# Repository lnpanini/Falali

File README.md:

# Falali — a 30.007 project

An AMR-style **under-ride platform** that drives beneath a textile trolley, uses upward-facing
time-of-flight sensors to confirm it is under the trolley and centred, **clamps** onto the
underside, and then moves the trolley. ESP32-S3 firmware, hardware and documentation.

This is also the whole-project home for **Falali — One AMR Fits All** (SUTD 30.007 Engineering
Design Innovation, Group 10): a low-profile autonomous mobile robot that moves existing fabric
trolleys in a textile factory by driving *underneath* them, clamping on, and transporting them —
no changes to the trolleys or the factory floor.

- **Controller:** ESP32-S3-WROOM-1 **N16R8** (16 MB flash, 8 MB octal PSRAM)
- **No** LiDAR, camera, ROS 2, SLAM, or mapping.

> **Hardware documentation lives in [`docs/hardware/`](docs/hardware/)** — power-up runbook,
> component list, per-connector pinouts for all three PCBs (extracted from the KiCad netlists, not
> inferred), and a fabrication/repair guide. [`docs/hardware-architecture.md`](docs/hardware-architecture.md)
> is the older companion and is partly superseded by it. The pin table further down this README is
> the *pre-PCB design intent* and does **not** match the fabricated board.

Full design: [`docs/superpowers/specs/2026-07-06-falali-esp32-docking-design.md`](docs/superpowers/specs/2026-07-06-falali-esp32-docking-design.md).

## Results against requirements

| Requirement | Target | Result |
|---|---|---|
| Fit under trolley clearance | ≤ 200 mm | **167 mm**, validated on the physical chassis |
| Move loaded trolley | ≥ 100 kg | **Passed — load moved with two people standing on top** |
| Clamp holding force | ≥ 300 N | Weakest-link analysis: clamp capacity 403 N (SF 1.34×) |
| Clamp vertical reach | ≥ 200 mm | Met |
| Docking time | ≤ 1 min | Under 60 s in testing |
| Worst-case castor misalignment | All 4 orientations | Moves under all |

Derivations, test protocols and data: [`docs/pdr-falali-amr.pdf`](docs/pdr-falali-amr.pdf)
(Preliminary Design Review deck, 11 Aug 2026).

## Delivered system

```
ESP-BASE (Wheel Drive PCB)                  ESP-ARM (Arm Subsystem PCB)
docking state machine                       arm axes X/Y, flipper servos, clamp
mecanum mixing, 4× corner ToF centring   ⇄  limit switches, homing
clamp handoff                             ESP-NOW over Wi-Fi (channel 1)

operator: BLE gamepad ([bench_ble/](bench_ble/))
```

Commercial AMRs don't fit this job: platform AMRs are too tall to get under the trolleys, tow
tractors need turning space, side-docking systems need the trolley modified. The answer is
**under-entry capture**: fit under the ≤200 mm clearance, strafe beneath an existing trolley with
mecanum drive, confirm centring sensor-only, clamp and carry.

## Safety principle

**The clamp must not engage unless the alignment logic CONFIRMS the platform is centred.** Limit
switches only confirm clamp *travel*; they never authorise clamping. `SafetyMonitor` is the single
gate (`confirmed && no faults && !E-stop`), and the docking state machine reaches the clamp handoff
only after a sustained `CONFIRM`. The clamp/arm mechanism itself is an **external subsystem** that
plugs in at the `IClamp` port.

## Architecture — hexagonal (ports & adapters)

```
lib/ports      pure C++ interfaces + shared types (no Arduino)
lib/domain     the hand-written core:  CornerEdgeDetector · DeadReckonOdometry · SafetyMonitor · DockingStateMachine
lib/drive      MecanumDrive (mixes body-frame vx/vy/omega -> 4 wheels)
lib/fakes      desktop test doubles for every port
lib/hal_esp32  Arduino adapters over popular libraries
include/       config.h (tunables) · pins.h (GPIO map)
src/main.cpp   composition root: builds adapters, wires domain, runs the loop
test/          host unit tests (Unity)
```

Dependency rule: **domain → ports** only; **adapters → ports**; **main → everything**. The domain
never includes Arduino, so it compiles and tests on a laptop. Commodity work uses popular libraries
(`pololu/VL53L0X`, `Bounce2`, `ArduinoJson`, `SerialCommands`, ESP32 `LEDC`); only the docking
sequence, corner edge detection, odometry, and safety logic are hand-written — and that is the part
under test.

**Alignment method:** with a solid trolley board and 4 corner ToF sensors, docking is a deterministic
geometric sequence — `APPROACH → ORIENT` (rotate until both front corners see the edge) `→ CENTER_X`
(odometry-centre between near/far edges) `→ CENTER_Y` (same, strafing) `→ CONFIRM → clamp handoff`.
Centring uses dead-reckoning odometry; driving to the midpoint between two edge events makes it robust
to calibration error.

**ToF wiring, both ESPs:** all four corner sensors keep their factory address `0x29` and are brought
up one at a time via **XSHUT re-addressing** — `Vl53l0xArray` on the base, `TofSensorArray` in
`arm/`. An earlier design multiplexed them through the PCA9548A breakout in
[`KiCad/PCA9548A Breakout/`](KiCad/PCA9548A%20Breakout/); final firmware uses no mux, and the
breakout is kept as history of that era.

## Build, test, flash

```bash
# Host unit tests of the pure core — no hardware needed:
pio test -e native

# Compile / upload the firmware (fetches lib_deps):
pio run -e esp32s3
pio run -e esp32s3 -t upload
pio device monitor -b 115200
```

Arm subsystem firmware has its own project: [`arm/`](arm/README.md).

## Operator interface — Xbox gamepad over BLE

**The robot is driven from a gamepad, not a serial console.** `bench_ble/` runs
Bluepad32, which owns stdin: `Console` is output-only and `Serial` is never
`begin()`-ed, so **typed commands cannot reach the firmware.** Every operator
control is a gamepad button. See [`docs/gotchas.md`](docs/gotchas.md) §6.

The base prints status to the console as it runs; that is one-way.

> A `DOCK`/`ABORT`/`UNCLAMP`/`STATUS` serial protocol was designed and the
> parser written, but it never ran on hardware — see **Project history** below.

## Pin map — ESP32-S3-N16R8

> ## 🛑 The table below is WRONG. Do not wire or flash from it.
>
> It is the **pre-PCB design intent** and does not match the fabricated board. On the real board
> GPIO4–7 are the **ToF XSHUT** lines, not wheel SV, and GPIO38/39 are **motor brake** lines, not
> I²C. Using this map would drive the I²C bus as motor enables.
>
> **The real map is [`include/pins.h`](include/pins.h)**, extracted from the KiCad netlist, with
> per-connector pinouts in [`docs/hardware/boards.md`](docs/hardware/boards.md).
>
> Kept here only because it is referenced by older notes. It should be deleted.

Reserved on the N16R8: **GPIO26–37** (flash + octal PSRAM) and **GPIO19/20** (USB-CDC).

| Group | Signals | GPIO |
|---|---|---|
| Wheel speed (SV, PWM) | FL/FR/RL/RR | 4, 5, 6, 7 |
| Wheel direction (F/R) | FL/FR/RL/RR | 15, 16, 17, 18 |
| Wheel enable / brake (ganged) | EN / BRK | 8 / 9 |
| Clamp (BTS7960) | RPWM / LPWM / EN | 11 / 12 / 13 |
| Clamp current sense (ADC1) | IS close / open | 1 / 2 |
| Limit switches | open / closed | 14 / 21 |
| ToF I²C | SDA / SCL | 38 / 39 |

## Hardware bring-up checklist (before trusting it under a trolley)

These adapters were validated on the assembled robot over the 2026 term. Kept as
a bring-up order for a rebuild, or after a board respin:

1. **PWM API** — a `PwmPin` shim supports Arduino-ESP32 core 2.x *and* 3.x automatically.
2. **BLD120A polarities** — `F/R` forward sense, and active-low `EN`/`BRK` (`Bld120aMotor.h`). There
   is no `ALARM`: the driver has no such terminal, only a front-panel LED.
3. **Mecanum + orient signs** — confirm forward / strafe / yaw directions (`MecanumDrive.cpp`) and the
   `ORIENT` rotate-direction sign in `DockingStateMachine.cpp` (rotate toward the lagging corner).
4. **ToF corners** — FL/FR/RL/RR on their XSHUT pins (`pins::kTofXSHUT`; `Vl53l0xArray` is the
   default backend since the mux approach was retired); set the board
   **height band** (`makeCornerConfig`).
5. **Odometry calibration** — measure `max_lin_mm_s` / `max_ang_rad_s` (`makeOdometryCal`); tune the
   centring tolerance/offsets in `makeDockConfig`.
6. **Per-wheel current sense** — calibrate `cfg::kWheelStallAmps` under a loaded trolley. Note the
   ACS758 outputs are **not currently wired** to J9/J12/J14/J17, so this reads nothing until they are
   ([`docs/hardware/components.md`](docs/hardware/components.md) §4). The clamp is on the *arm* board,
   not this one.
7. **Dry-run the alignment** and watch the JSON telemetry (`corners`, `x_mm`, `y_mm`, `confirmed`). The
   clamp/arm subsystem is external and validated separately at the `IClamp` handoff.

## Custom PCBs

Connector-level references for all boards (every pin extracted from the KiCad netlists):
[`docs/hardware/boards.md`](docs/hardware/boards.md).

| Board | Size | KiCad project | Job |
|---|---|---|---|
| **Wheel Drive PCB** | 130 × 105 mm | [`KiCad/Wheel Drive PCB/`](KiCad/Wheel%20Drive%20PCB/) | base ESP + 4 motor-driver adapters + all base sensors |
| **Driver PCB** ×4 | 42.8 × 33.8 mm | [`KiCad/Driver PCB/`](KiCad/Driver%20PCB/) | 3.3 V → open-collector adapter, one per motor |
| **Arm Subsystem PCB** | 110 × 110 mm | [`KiCad/Arm Subsystem PCB/`](KiCad/Arm%20Subsystem%20PCB/) | arm ESP + 2 H-bridges + servos + 8 limit switches |
| PCA9548A breakout | — | [`KiCad/PCA9548A Breakout/`](KiCad/PCA9548A%20Breakout/) | I²C mux — **historical**, see ToF note above |

JLCPCB fab outputs ship with each project (`fab-output/` folders; the Arm board's zip is in its
folder). Board designs by Kai Xiang & Heng Li (arm/wheel sensor side) and Bryan Lim (base).

## Demos

| | |
|---|---|
| <video src="docs/media/videos/load-test-100kg.mp4" controls width="320"> | **Load test** — ≥100 kg requirement load, two people on top |
| <video src="docs/media/videos/wheel-subsystem-driving.mp4" controls width="320"> | Mecanum base driving and strafing |
| <video src="docs/media/videos/arm-subsystem-demo.mp4" controls width="320"> | Arm extension / flipper / release sequence |
| <video src="docs/media/videos/clamped-on-trolley.mp4" controls width="320"> | Clamped onto a trolley |

*(GitHub renders `<video>` tags in markdown; if your viewer doesn't, open the files under
[`docs/media/videos/`](docs/media/videos/).)*

<details>
<summary>All clips kept in the repo</summary>

| File | What it shows |
|---|---|
| [`trolley-carry-demo.mp4`](docs/media/videos/trolley-carry-demo.mp4) | full trolley-carry run (1:49) |
| [`clamping-on-sequence.mp4`](docs/media/videos/clamping-on-sequence.mp4) | clamp engaging under the trolley (0:56) |
| [`rail-strength-test.mp4`](docs/media/videos/rail-strength-test.mp4) | rail strength durability test (0:29) |
| [`img-3340.mp4`](docs/media/videos/img-3340.mp4) | bench footage (0:51) |
| [`img-3350.mp4`](docs/media/videos/img-3350.mp4) | bench footage (0:43) |
| [`video-2026-07-13.mp4`](docs/media/videos/video-2026-07-13.mp4) | mid-build progress clip (0:16) |
| [`video-2026-07-17.mp4`](docs/media/videos/video-2026-07-17.mp4) | mid-build progress clip (0:10) |
| [`clip-20260707.mp4`](docs/media/videos/clip-20260707.mp4) | early drive test (0:05) |

</details>

### Function diagrams

| System flow | Arm subsystem |
|---|---|
|  |  |

*(SVGs render inline above; click through for the higher-resolution PNGs.)*

<details>
<summary>More photos</summary>

| | | |
|---|---|---|
|  |  |  |
|  | | |

All photos: [`docs/media/photos/`](docs/media/photos/).
</details>

## Team — Group 10

| Member | Focus areas |
|---|---|
| Chan Long Nam | mechanical structure & clamping system |
| Chong Shao Yih | chassis & integration |
| [Chua Heng Li](https://github.com/chuahengli) | electronics: arm-subsystem & wheel-drive PCBs, power wiring, arm firmware |
| Jacelyn Tan | systems analysis & testing |
| Lim Nguyen Ping, Bryan | drive firmware, sensing & base architecture (this repo) |
| Lucas Lim Kong Keong | clamping mechanism & materials |
| Soh Kai Siang | power distribution & wiring; co-author of arm firmware |

*Rows are initial attributions — each member, feel free to refine your own.*

## Repository map

| Path | What it is |
|---|---|
| [`src/`](src/README.md) | firmware entry + bench bring-up sketches |
| [`lib/`](lib/README.md) | hexagonal core: ports, domain, drive, fakes, ESP32 adapters |
| [`include/`](include/config.h) | tunables (`config.h`) and GPIO map (`pins.h`) |
| [`test/`](test/README.md) | host unit tests (Unity, `pio test -e native`) |
| [`arm/`](arm/README.md) | vendored arm-subsystem firmware (ESP-NOW slave) |
| [`KiCad/`](KiCad/README.md) | four custom board projects + fab outputs |
| [`bench_ble/`](bench_ble/README.md) | BLE-gamepad bench firmware |
| [`tools/`](tools/README.md) | PCB production test |
| [`docs/`](docs/) | specs, gotchas, hardware references, runbooks, session history, media |

## Project history — what was tried and dropped

Kept because knowing what was *attempted* saves repeating it. None of the below
is part of the delivered machine.

| Abandoned | What it was | Why it went |
|---|---|---|
| **AS5600 wheel encoders** | four magnetic encoders, one per wheel, for closed-loop speed | Never worked on the fabricated board: pin 1 of every 1×04 encoder header is unconnected, and all four parts share address `0x36` on a commoned bus. The sensors and shaft magnets are **still physically mounted on the motors**, unwired and undriven. [`docs/gotchas.md`](docs/gotchas.md) §13 |
| **TCA9548A / PCA9548A I²C mux** | fitted to give the four encoders separate addresses | Went with the encoders. An external PCA9548-type mux overheated and failed with more than two AS5600 attached. The ToF sensors never needed it — they use XSHUT re-addressing. Board files kept at [`KiCad/PCA9548A Breakout/`](KiCad/PCA9548A%20Breakout/) |
| **Raspberry Pi 5 as main controller** | Pi 5 driving two ESP32s over USB serial, with a link watchdog | Never used. The delivered prototype runs on the two ESP32s alone, base ↔ arm over ESP-NOW. Design retained at [`docs/superpowers/specs/2026-08-04-rpi5-main-controller-design.md`](docs/superpowers/specs/2026-08-04-rpi5-main-controller-design.md) |
| **`DOCK`/`ABORT`/`UNCLAMP`/`STATUS` serial protocol** | text commands in, JSON telemetry out | The parser was written but Bluepad32 owns stdin, so it never ran. Operator control is the gamepad. [`docs/gotchas.md`](docs/gotchas.md) §6 |
| **Hardware E-stop input** | a GPIO for an emergency-stop button | Discussed, never implemented. The red mushroom button on the robot is wired as an **enable** for the 12 V arm rail — [`docs/hardware/startup.md`](docs/hardware/startup.md) §1 |
| **Base-board clamp driver** | BTS7960 clamp driven from the base ESP | Moved to the arm subsystem. The base pins remain `kNoPin` so the one-ESP firmware still compiles |

Code for the encoders, the mux and the Pi was **deleted on 2026-08-31** rather
than left to rot — `git log --diff-filter=D` recovers any of it. What was worth
keeping is the analysis of *why* each failed, which lives in
[`docs/gotchas.md`](docs/gotchas.md) and [`docs/hardware/`](docs/hardware/).

## Acknowledgements

- Course 30.007 Engineering Design Innovation, SUTD; reviewed by Prof. Bradley Camburn and Prof. Wai Lee Chan
- Firmware drafting and design-analysis support used AI tooling (Claude, Gemini), as disclosed in the PDR

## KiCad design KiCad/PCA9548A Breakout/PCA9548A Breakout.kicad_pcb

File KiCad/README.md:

# KiCad/ — custom PCB projects

Connector-level references for every board (extracted from these netlists):
[`docs/hardware/boards.md`](../docs/hardware/boards.md).

| Project | Size | Job |
|---|---|---|
| [`Wheel Drive PCB/`](Wheel%20Drive%20PCB/) | 130 × 105 mm | base ESP + 4× Driver PCB headers + all base sensors |
| [`Driver PCB/`](Driver%20PCB/) | 42.8 × 33.8 mm | 3.3 V → open-collector adapter for the BLD-120A, one per motor (need 4) |
| [`Arm Subsystem PCB/`](Arm%20Subsystem%20PCB/) | 110 × 110 mm | arm ESP + 2 BTS7960 H-bridges + servo power + 8 limit-switch headers |
| [`PCA9548A Breakout/`](PCA9548A%20Breakout/) | — | 8-ch I²C mux — historical; final firmware uses XSHUT re-addressing instead |

## Board renders

Every board carries schematic / PCB-layout / 3D-view images next to its sources
(the Driver PCB keeps its design-history set under `preview/`). Thumbnails below
are embedded — click any image for the full-resolution file:

| Board | Schematic | PCB layout | 3D view |
|---|---|---|---|
| Wheel Drive PCB |  |  |  |
| Driver PCB ×4 | — |  |  |
| Arm Subsystem PCB |  |  |  |
| PCA9548A breakout |  |  |  |

More Driver PCB renders — design history (placement, routing progress, copper
layers; click to open):

| | | |
|---|---|---|
|  |  |  |
|  |  |  |

Connector-level pin tables live in
[`docs/hardware/boards.md`](../docs/hardware/boards.md); these renders are the
visual companion to that reference.

Each project folder carries the KiCad sources (`.kicad_pro/.kicad_sch/.kicad_pcb`),
the extracted netlist (`.net`), schematic/PCB/3D renders as PNG, and JLCPCB fab
outputs (`fab-output/`; the Arm board's are zipped). Board designs: Kai Xiang &
Heng Li (Arm Subsystem, PCA9548A breakout), Bryan Lim (Wheel Drive, Driver).

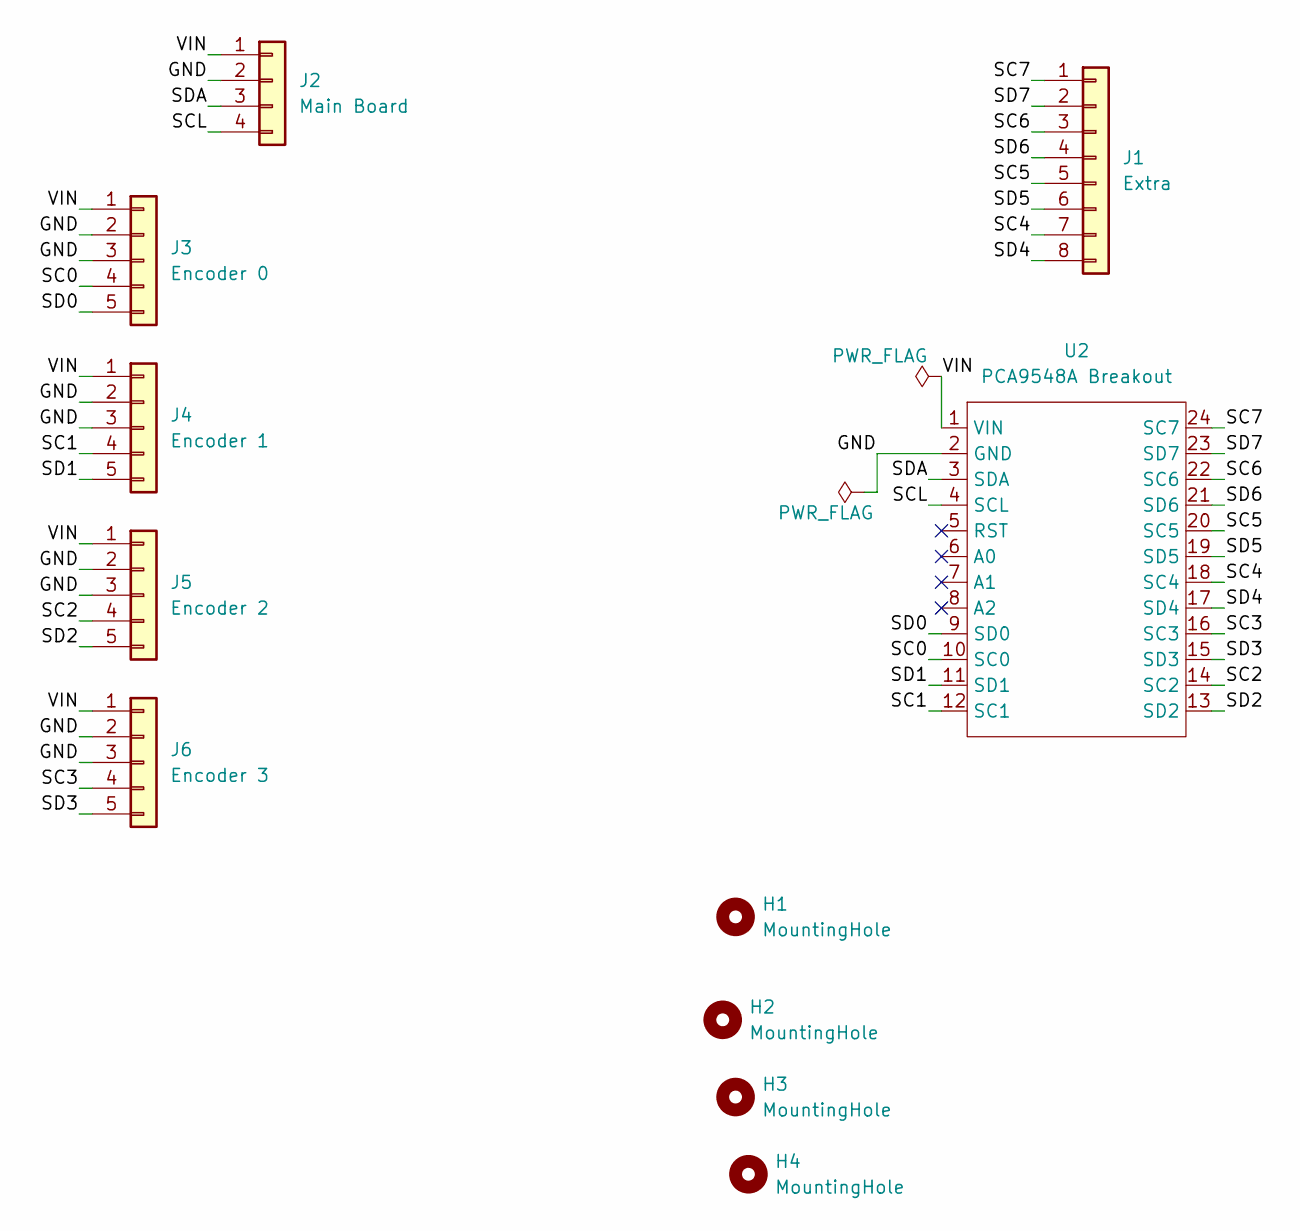
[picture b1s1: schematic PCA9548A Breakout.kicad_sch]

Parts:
H1, H2, H3, H4: MountingHole; MountingHole_3.2mm_M3
J1: Extra; PinHeader_1x08_P2.54mm_Vertical
J2: Main Board; PinHeader_1x04_P2.54mm_Vertical
J3: Encoder 0; PinHeader_1x05_P2.54mm_Vertical
J4: Encoder 1; PinHeader_1x05_P2.54mm_Vertical
J5: Encoder 2; PinHeader_1x05_P2.54mm_Vertical
J6: Encoder 3; PinHeader_1x05_P2.54mm_Vertical
U2: PCA9548A Breakout

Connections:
/GND: J2.2, J3.2, J3.3, J4.2, J4.3, J5.2, J5.3, J6.2, J6.3, U2.2 (GND)
/SC0: J3.4, U2.10 (SC0)
/SC1: J4.4, U2.12 (SC1)
/SC2: J5.4, U2.14 (SC2)
/SC3: J6.4, U2.16 (SC3)
/SC4: J1.7, U2.18 (SC4)
/SC5: J1.5, U2.20 (SC5)
/SC6: J1.3, U2.22 (SC6)
/SC7: J1.1, U2.24 (SC7)
/SCL: J2.4, U2.4 (SCL)
/SD0: J3.5, U2.9 (SD0)
/SD1: J4.5, U2.11 (SD1)
/SD2: J5.5, U2.13 (SD2)
/SD3: J6.5, U2.15 (SD3)
/SD4: J1.8, U2.17 (SD4)
/SD5: J1.6, U2.19 (SD5)
/SD6: J1.4, U2.21 (SD6)
/SD7: J1.2, U2.23 (SD7)
/SDA: J2.3, U2.3 (SDA)
/VIN: J2.1, J3.1, J4.1, J5.1, J6.1, U2.1 (VIN)

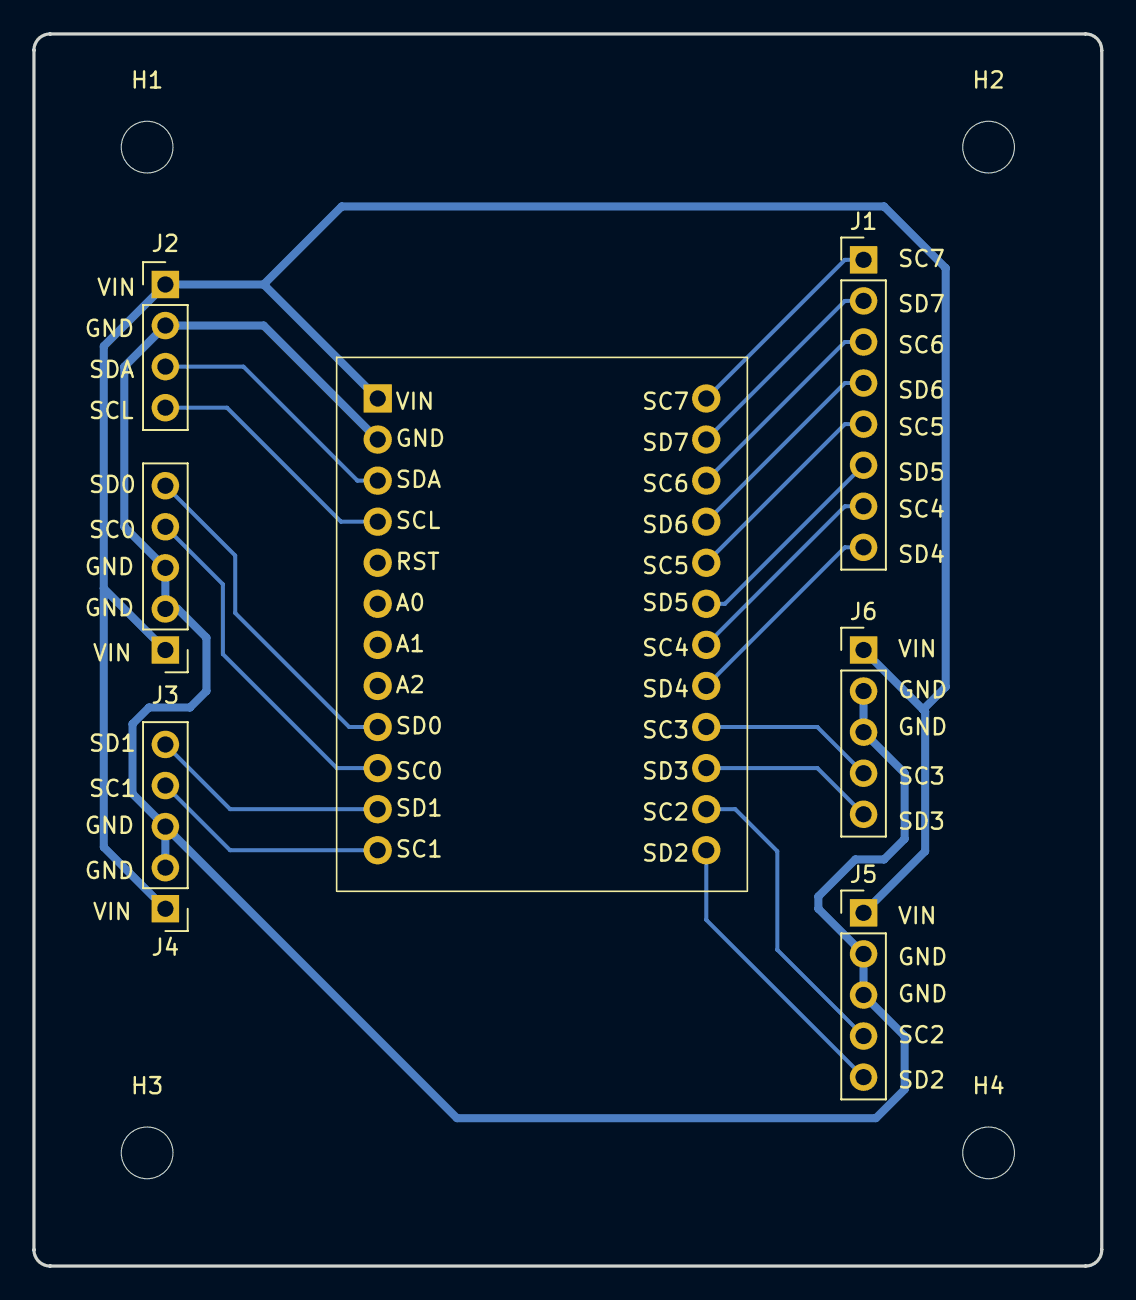
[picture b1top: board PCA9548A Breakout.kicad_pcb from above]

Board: 2 copper layers, 66.0 x 76.2 mm, 11 parts (0 on the bottom side), 20 nets.

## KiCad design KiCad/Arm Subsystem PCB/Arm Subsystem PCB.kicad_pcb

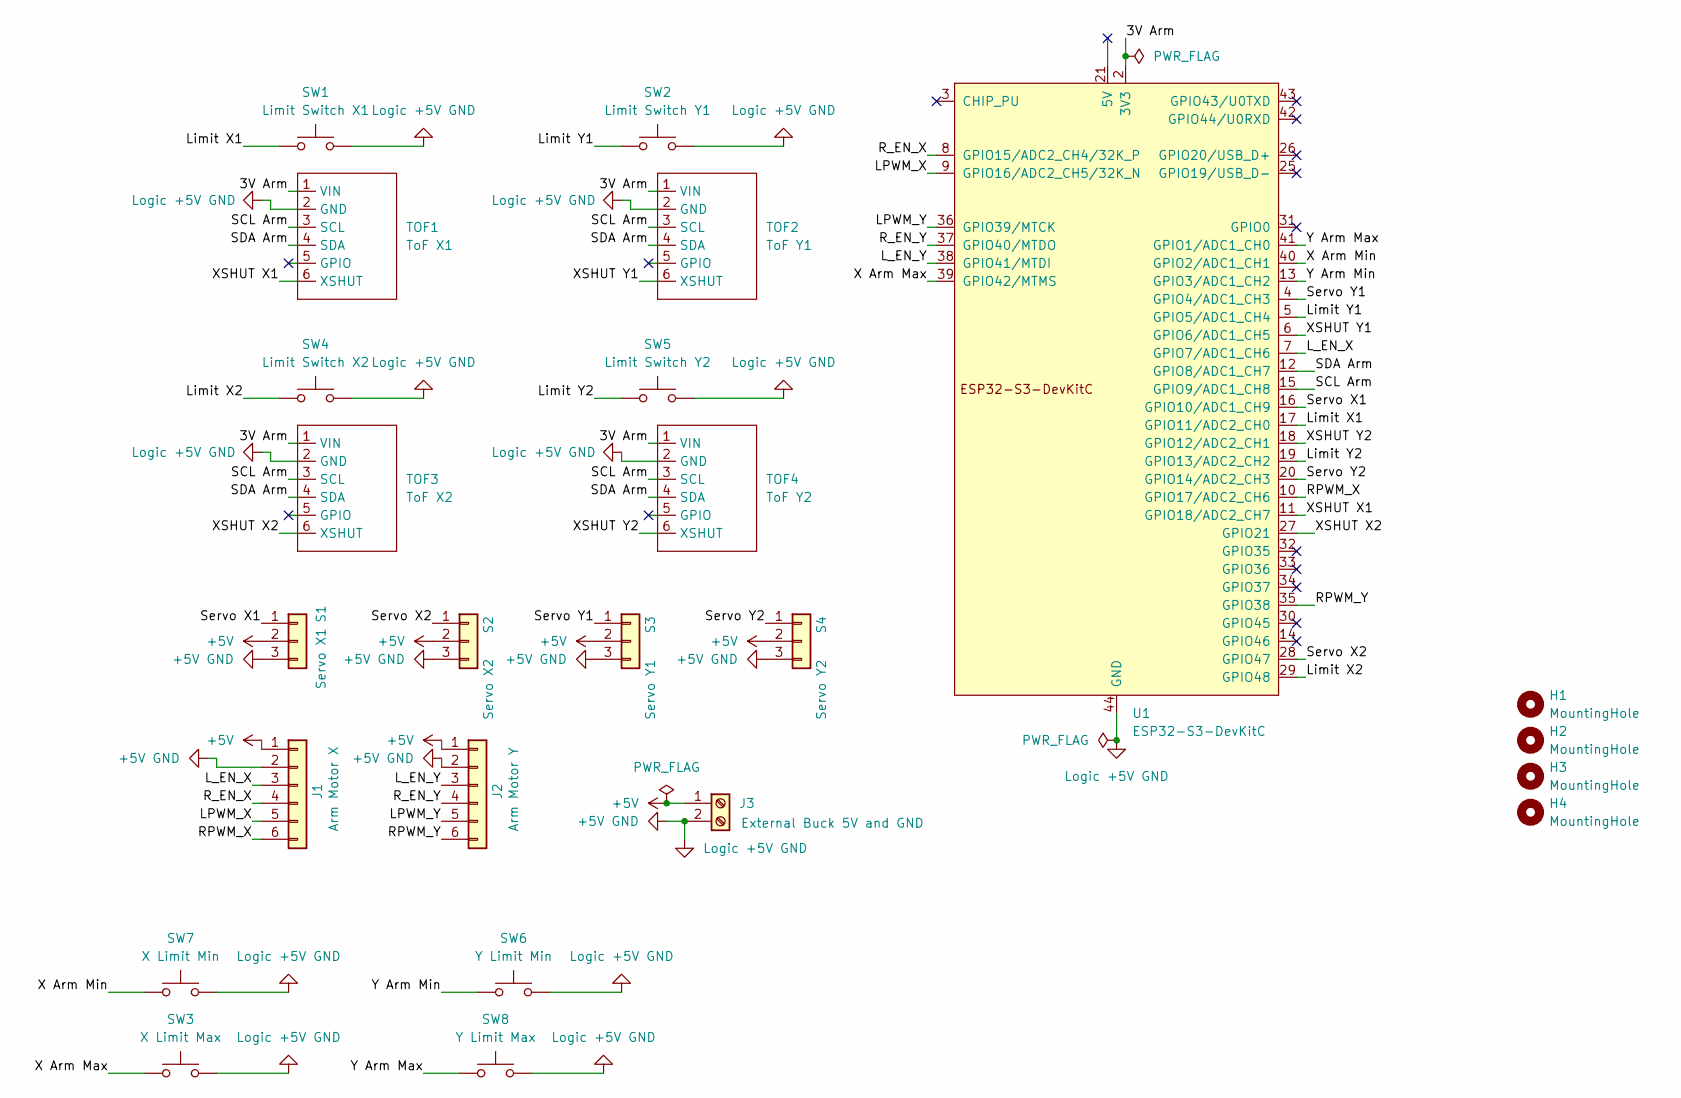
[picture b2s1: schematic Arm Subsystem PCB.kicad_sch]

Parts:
H1, H2, H3, H4: MountingHole; MountingHole_3.2mm_M3
J1: Arm Motor X; PinHeader_1x06_P2.54mm_Vertical
J2: Arm Motor Y; PinHeader_1x06_P2.54mm_Vertical
J3: External Buck 5V and GND; TerminalBlock_Phoenix_MKDS-1,5-2-5.08_1x02_P5.08mm_Horizont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
S1: Servo X1; PinHeader_1x03_P2.54mm_Vertical
S2: Servo X2; PinHeader_1x03_P2.54mm_Vertical
S3: Servo Y1; PinHeader_1x03_P2.54mm_Vertical
S4: Servo Y2; PinHeader_1x03_P2.54mm_Vertical
SW1: Limit Switch X1; PinHeader_1x02_P2.54mm_Vertical
SW2: Limit Switch Y1; PinHeader_1x02_P2.54mm_Vertical
SW3: X Limit Max; PinHeader_1x02_P2.54mm_Vertical
SW4: Limit Switch X2; PinHeader_1x02_P2.54mm_Vertical
SW5: Limit Switch Y2; PinHeader_1x02_P2.54mm_Vertical
SW6: Y Limit Min; PinHeader_1x02_P2.54mm_Vertical
SW7: X Limit Min; PinHeader_1x02_P2.54mm_Vertical
SW8: Y Limit Max; PinHeader_1x02_P2.54mm_Vertical
TOF1: ToF X1; PinHeader_1x06_P2.54mm_Vertical
TOF2: ToF Y1; PinHeader_1x06_P2.54mm_Vertical
TOF3: ToF X2; PinHeader_1x06_P2.54mm_Vertical
TOF4: ToF Y2; PinHeader_1x06_P2.54mm_Vertical
U1: ESP32-S3-DevKitC; ESP32-S3-DevKitC-N16R8

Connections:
+5V: J1.1, J2.1, J3.1, S1.2, S2.2, S3.2, S4.2
+5V GND: J1.2, J2.2, J3.2, S1.3, S2.3, S3.3, S4.3, SW1.2, SW2.2, SW3.2, SW4.2, SW5.2, SW6.2, SW7.2, SW8.2, TOF1.2 (GND), TOF2.2 (GND), TOF3.2 (GND), TOF4.2 (GND), U1.22 (GND), U1.23 (GND), U1.24 (GND), U1.44 (GND)
/3V Arm: TOF1.1 (VIN), TOF2.1 (VIN), TOF3.1 (VIN), TOF4.1 (VIN), U1.1 (3V3), U1.2 (3V3)
/LPWM_X: J1.5, U1.9 (GPIO16/ADC2_CH5/32K_N)
/LPWM_Y: J2.5, U1.36 (GPIO39/MTCK)
/L_EN_X: J1.3, U1.7 (GPIO7/ADC1_CH6)
/L_EN_Y: J2.3, U1.38 (GPIO41/MTDI)
/Limit X1: SW1.1, U1.17 (GPIO11/ADC2_CH0)
/Limit X2: SW4.1, U1.29 (GPIO48)
/Limit Y1: SW2.1, U1.5 (GPIO5/ADC1_CH4)
/Limit Y2: SW5.1, U1.19 (GPIO13/ADC2_CH2)
/RPWM_X: J1.6, U1.10 (GPIO17/ADC2_CH6)
/RPWM_Y: J2.6, U1.35 (GPIO38)
/R_EN_X: J1.4, U1.8 (GPIO15/ADC2_CH4/32K_P)
/R_EN_Y: J2.4, U1.37 (GPIO40/MTDO)
/SCL Arm: TOF1.3 (SCL), TOF2.3 (SCL), TOF3.3 (SCL), TOF4.3 (SCL), U1.15 (GPIO9/ADC1_CH8)
/SDA Arm: TOF1.4 (SDA), TOF2.4 (SDA), TOF3.4 (SDA), TOF4.4 (SDA), U1.12 (GPIO8/ADC1_CH7)
/Servo X1: S1.1, U1.16 (GPIO10/ADC1_CH9)
/Servo X2: S2.1, U1.28 (GPIO47)
/Servo Y1: S3.1, U1.4 (GPIO4/ADC1_CH3)
/Servo Y2: S4.1, U1.20 (GPIO14/ADC2_CH3)
/X Arm Max: SW3.1, U1.39 (GPIO42/MTMS)
/X Arm Min: SW7.1, U1.40 (GPIO2/ADC1_CH1)
/XSHUT X1: TOF1.6 (XSHUT), U1.11 (GPIO18/ADC2_CH7)
/XSHUT X2: TOF3.6 (XSHUT), U1.27 (GPIO21)
/XSHUT Y1: TOF2.6 (XSHUT), U1.6 (GPIO6/ADC1_CH5)
/XSHUT Y2: TOF4.6 (XSHUT), U1.18 (GPIO12/ADC2_CH1)
/Y Arm Max: SW8.1, U1.41 (GPIO1/ADC1_CH0)
/Y Arm Min: SW6.1, U1.13 (GPIO3/ADC1_CH2)

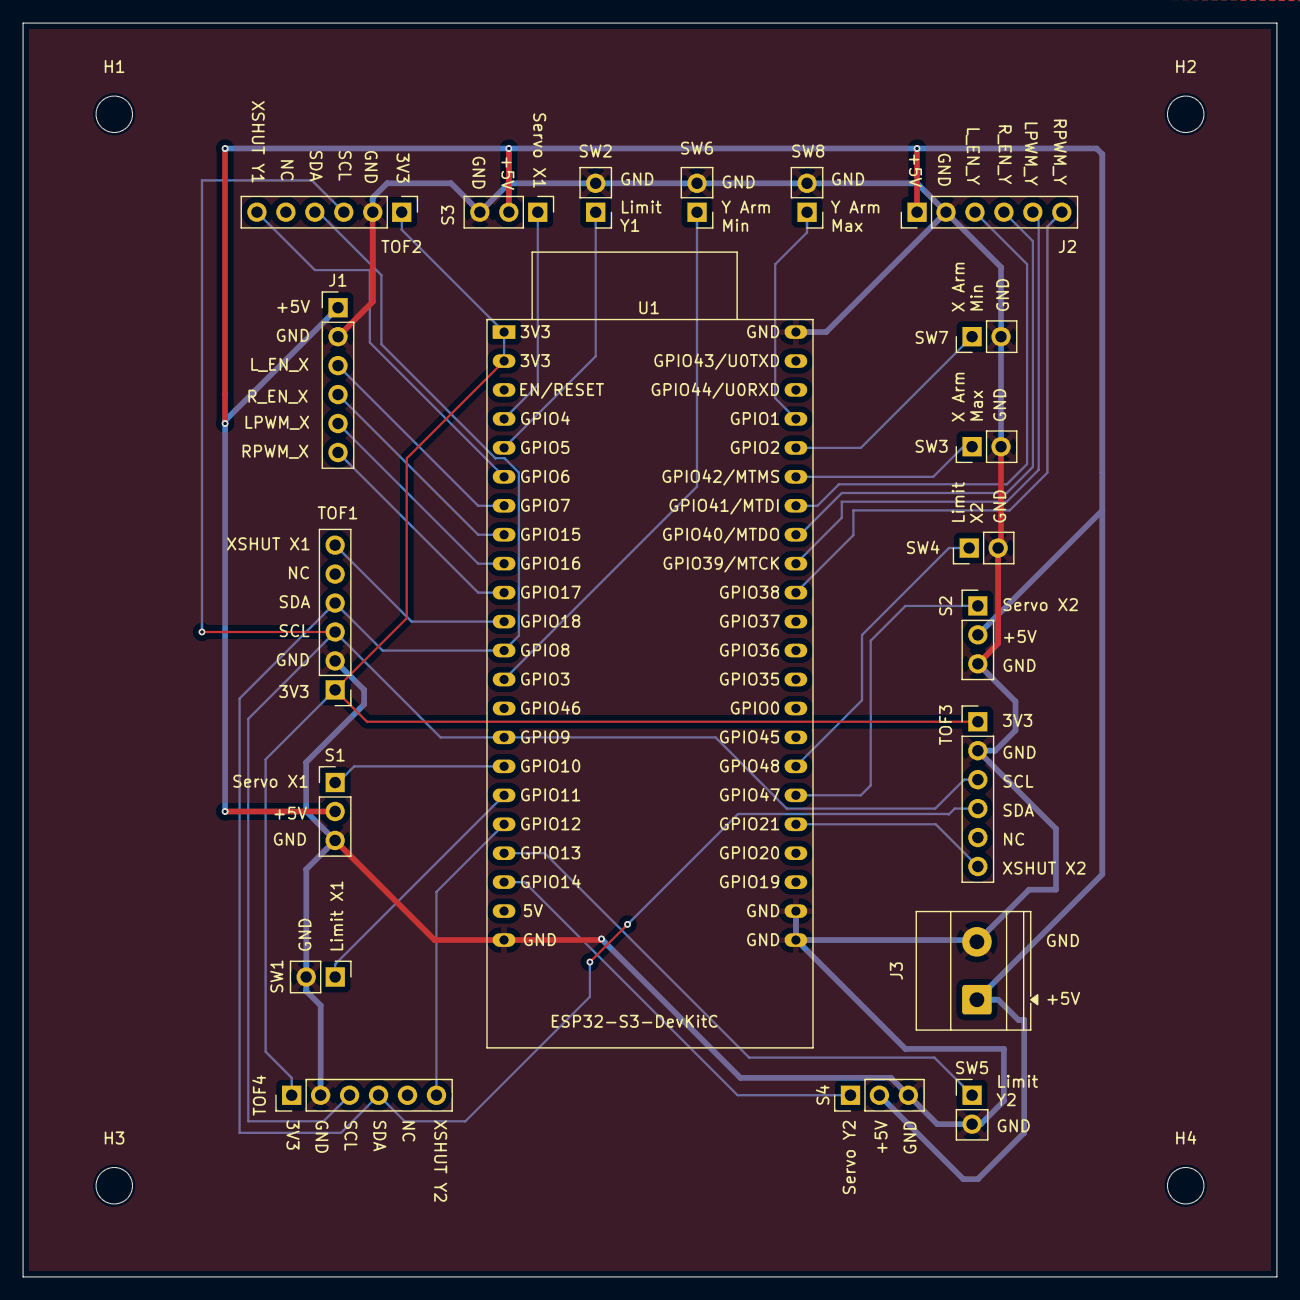
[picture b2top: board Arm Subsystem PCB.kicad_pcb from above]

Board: 2 copper layers, 110.0 x 110.0 mm, 24 parts (0 on the bottom side), 29 nets.

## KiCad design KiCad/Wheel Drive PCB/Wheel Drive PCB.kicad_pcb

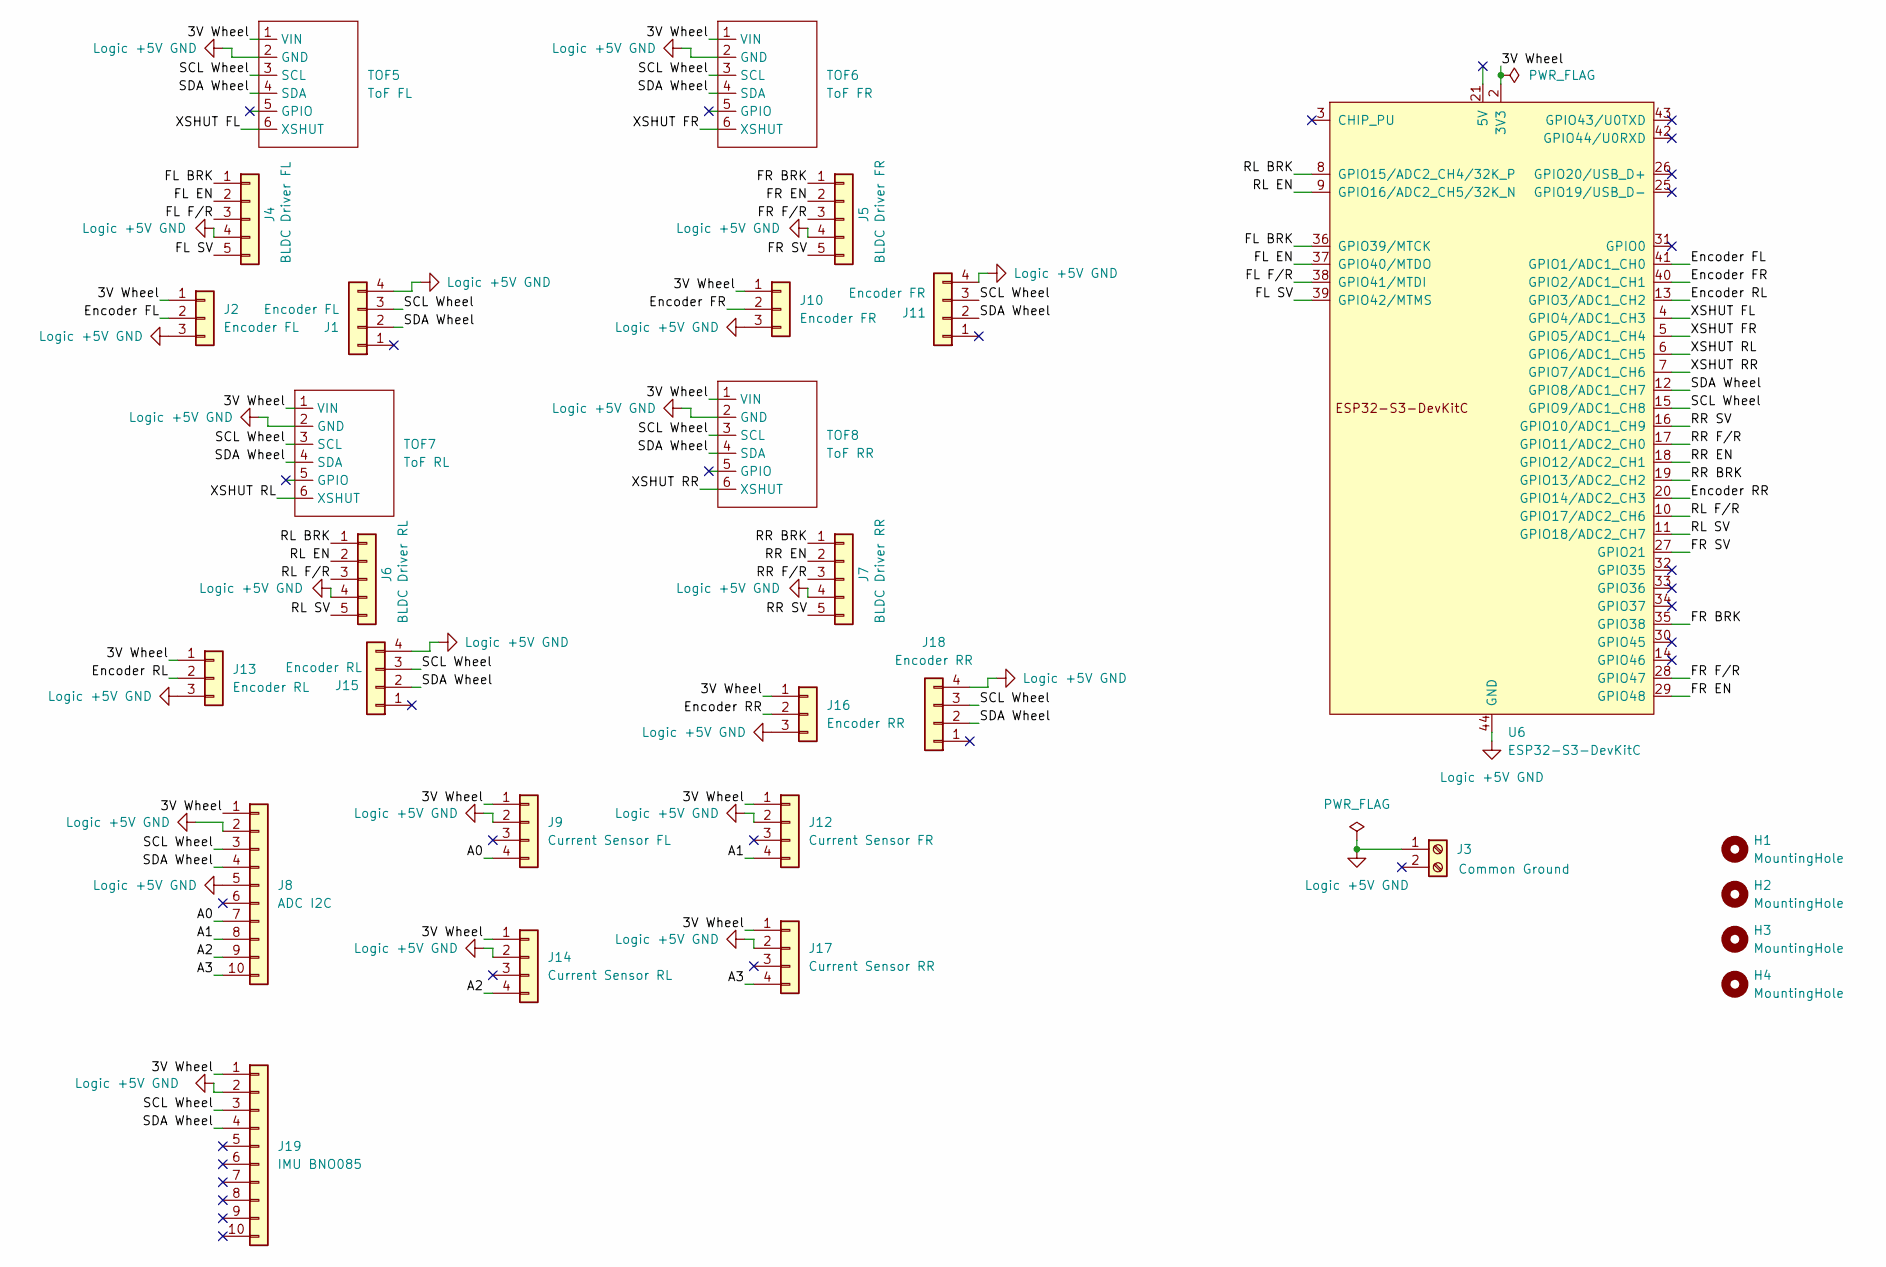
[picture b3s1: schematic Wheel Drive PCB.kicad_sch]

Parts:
H1, H2, H3, H4: MountingHole; MountingHole_3.2mm_M3
J1: Encoder FL; PinHeader_1x04_P2.54mm_Vertical
J2: Encoder FL; PinHeader_1x03_P2.54mm_Vertical
J3: Common Ground; TerminalBlock_Phoenix_MKDS-1,5-2-5.08_1x02_P5.08mm_Horizont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
J4: BLDC Driver FL; PinHeader_1x05_P2.54mm_Vertical
J5: BLDC Driver FR; PinHeader_1x05_P2.54mm_Vertical
J6: BLDC Driver RL; PinHeader_1x05_P2.54mm_Vertical
J7: BLDC Driver RR; PinHeader_1x05_P2.54mm_Vertical
J8: ADC I2C; PinHeader_1x10_P2.54mm_Vertical
J9: Current Sensor FL; PinHeader_1x04_P2.54mm_Vertical
J10: Encoder FR; PinHeader_1x03_P2.54mm_Vertical
J11: Encoder FR; PinHeader_1x04_P2.54mm_Vertical
J12: Current Sensor FR; PinHeader_1x04_P2.54mm_Vertical
J13: Encoder RL; PinHeader_1x03_P2.54mm_Vertical
J14: Current Sensor RL; PinHeader_1x04_P2.54mm_Vertical
J15: Encoder RL; PinHeader_1x04_P2.54mm_Vertical
J16: Encoder RR; PinHeader_1x03_P2.54mm_Vertical
J17: Current Sensor RR; PinHeader_1x04_P2.54mm_Vertical
J18: Encoder RR; PinHeader_1x04_P2.54mm_Vertical
J19: IMU BNO085; PinHeader_1x10_P2.54mm_Vertical
TOF5: ToF FL; PinHeader_1x06_P2.54mm_Vertical
TOF6: ToF FR; PinHeader_1x06_P2.54mm_Vertical
TOF7: ToF RL; PinHeader_1x06_P2.54mm_Vertical
TOF8: ToF RR; PinHeader_1x06_P2.54mm_Vertical
U6: ESP32-S3-DevKitC; ESP32-S3-DevKitC-N16R8

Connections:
/3V Wheel: J2.1, J8.1, J9.1, J10.1, J12.1, J13.1, J14.1, J16.1, J17.1, J19.1, TOF5.1 (VIN), TOF6.1 (VIN), TOF7.1 (VIN), TOF8.1 (VIN), U6.1 (3V3), U6.2 (3V3)
/A0: J8.7, J9.4
/A1: J8.8, J12.4
/A2: J8.9, J14.4
/A3: J8.10, J17.4
/Encoder FL: J2.2, U6.41 (GPIO1/ADC1_CH0)
/Encoder FR: J10.2, U6.40 (GPIO2/ADC1_CH1)
/Encoder RL: J13.2, U6.13 (GPIO3/ADC1_CH2)
/Encoder RR: J16.2, U6.20 (GPIO14/ADC2_CH3)
/FL BRK: J4.1, U6.36 (GPIO39/MTCK)
/FL EN: J4.2, U6.37 (GPIO40/MTDO)
/FL F/R: J4.3, U6.38 (GPIO41/MTDI)
/FL SV: J4.5, U6.39 (GPIO42/MTMS)
/FR BRK: J5.1, U6.35 (GPIO38)
/FR EN: J5.2, U6.29 (GPIO48)
/FR F/R: J5.3, U6.28 (GPIO47)
/FR SV: J5.5, U6.27 (GPIO21)
/RL BRK: J6.1, U6.8 (GPIO15/ADC2_CH4/32K_P)
/RL EN: J6.2, U6.9 (GPIO16/ADC2_CH5/32K_N)
/RL F/R: J6.3, U6.10 (GPIO17/ADC2_CH6)
/RL SV: J6.5, U6.11 (GPIO18/ADC2_CH7)
/RR BRK: J7.1, U6.19 (GPIO13/ADC2_CH2)
/RR EN: J7.2, U6.18 (GPIO12/ADC2_CH1)
/RR F/R: J7.3, U6.17 (GPIO11/ADC2_CH0)
/RR SV: J7.5, U6.16 (GPIO10/ADC1_CH9)
/SCL Wheel: J1.3, J8.3, J11.3, J15.3, J18.3, J19.3, TOF5.3 (SCL), TOF6.3 (SCL), TOF7.3 (SCL), TOF8.3 (SCL), U6.15 (GPIO9/ADC1_CH8)
/SDA Wheel: J1.2, J8.4, J11.2, J15.2, J18.2, J19.4, TOF5.4 (SDA), TOF6.4 (SDA), TOF7.4 (SDA), TOF8.4 (SDA), U6.12 (GPIO8/ADC1_CH7)
/XSHUT FL: TOF5.6 (XSHUT), U6.4 (GPIO4/ADC1_CH3)
/XSHUT FR: TOF6.6 (XSHUT), U6.5 (GPIO5/ADC1_CH4)
/XSHUT RL: TOF7.6 (XSHUT), U6.6 (GPIO6/ADC1_CH5)
/XSHUT RR: TOF8.6 (XSHUT), U6.7 (GPIO7/ADC1_CH6)
Logic +5V GND: J1.4, J2.3, J3.1, J4.4, J5.4, J6.4, J7.4, J8.2, J8.5, J9.2, J10.3, J11.4, J12.2, J13.3, J14.2, J15.4, J16.3, J17.2, J18.4, J19.2, TOF5.2 (GND), TOF6.2 (GND), TOF7.2 (GND), TOF8.2 (GND), U6.22 (GND), U6.23 (GND), U6.24 (GND), U6.44 (GND)

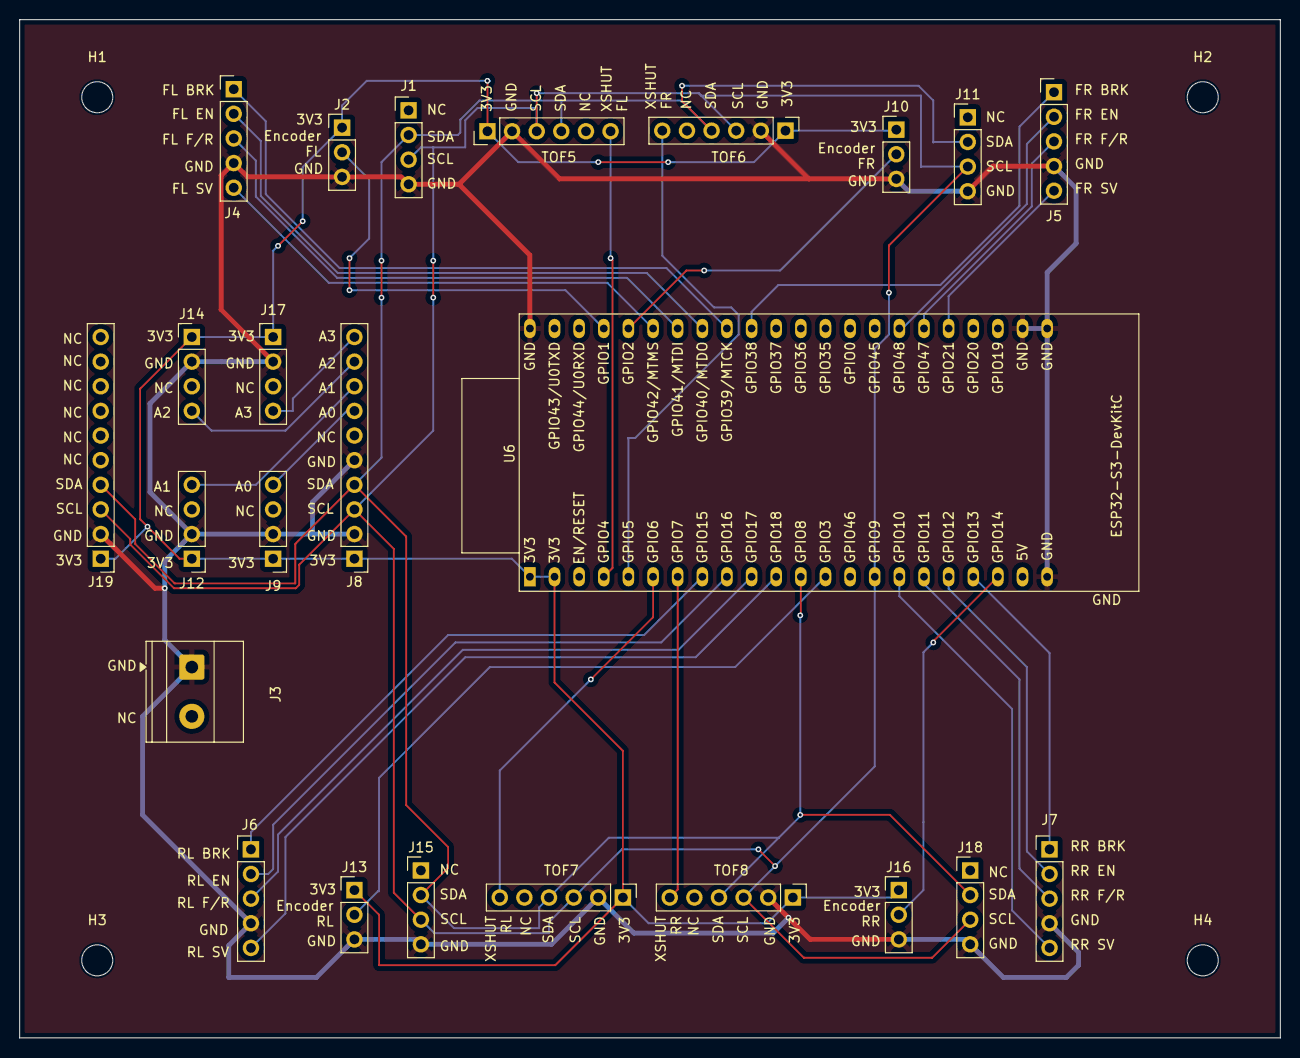
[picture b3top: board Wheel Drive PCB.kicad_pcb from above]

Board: 2 copper layers, 130.0 x 105.0 mm, 28 parts (0 on the bottom side), 32 nets.

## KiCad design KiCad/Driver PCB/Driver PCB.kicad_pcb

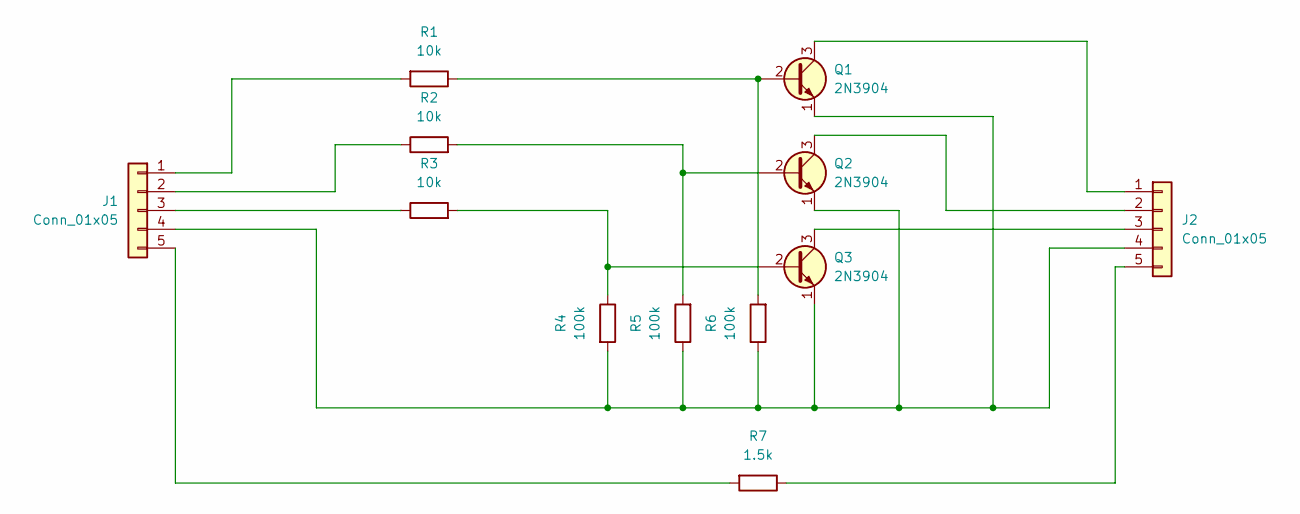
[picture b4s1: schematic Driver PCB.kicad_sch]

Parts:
J1, J2: Conn_01x05; PinHeader_1x05_P2.54mm_Vertical
Q1, Q2, Q3: 2N3904; TO-92_Inline_Wide_EBC
R1, R2, R3: 10k; R_Axial_DIN0207_L6.3mm_D2.5mm_P7.62mm_Horizontal
R4, R5, R6: 100k; R_Axial_DIN0207_L6.3mm_D2.5mm_P7.62mm_Horizontal
R7: 1.5k; R_Axial_DIN0207_L6.3mm_D2.5mm_P7.62mm_Horizontal

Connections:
unnamed: J1.1, R1.2
unnamed: J1.2, R2.1
unnamed: J1.3, R3.1
unnamed: J1.4, J2.4, Q1.1 (E), Q2.1 (E), Q3.1 (E), R4.2, R5.1, R6.1
unnamed: J1.5, R7.2
unnamed: J2.1, Q1.3 (C)
unnamed: J2.2, Q2.3 (C)
unnamed: J2.3, Q3.3 (C)
unnamed: J2.5, R7.1
unnamed: Q1.2 (B), R1.1, R6.2
unnamed: Q2.2 (B), R2.2, R5.2
unnamed: Q3.2 (B), R3.2, R4.1

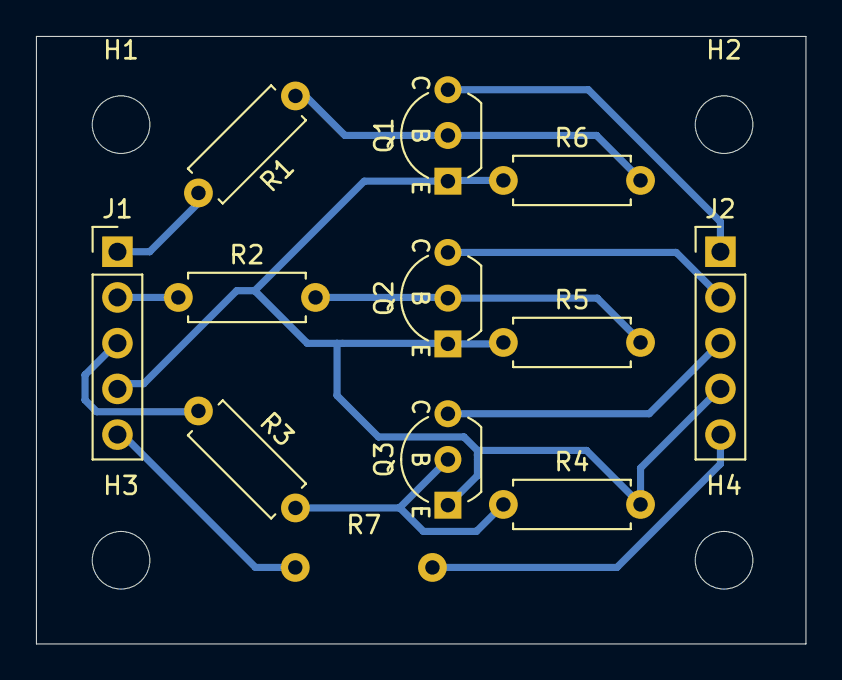
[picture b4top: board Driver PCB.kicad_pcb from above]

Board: 2 copper layers, 42.8 x 33.8 mm, 16 parts (1 on the bottom side), 12 nets.

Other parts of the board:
H1, H2, H3, H4: MountingHole_3.2mm_M3
